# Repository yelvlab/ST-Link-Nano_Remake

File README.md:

# ST-Link-Nano_Remake
对稚晖君的ST-Link-Nano项目重新绘图和布局布线

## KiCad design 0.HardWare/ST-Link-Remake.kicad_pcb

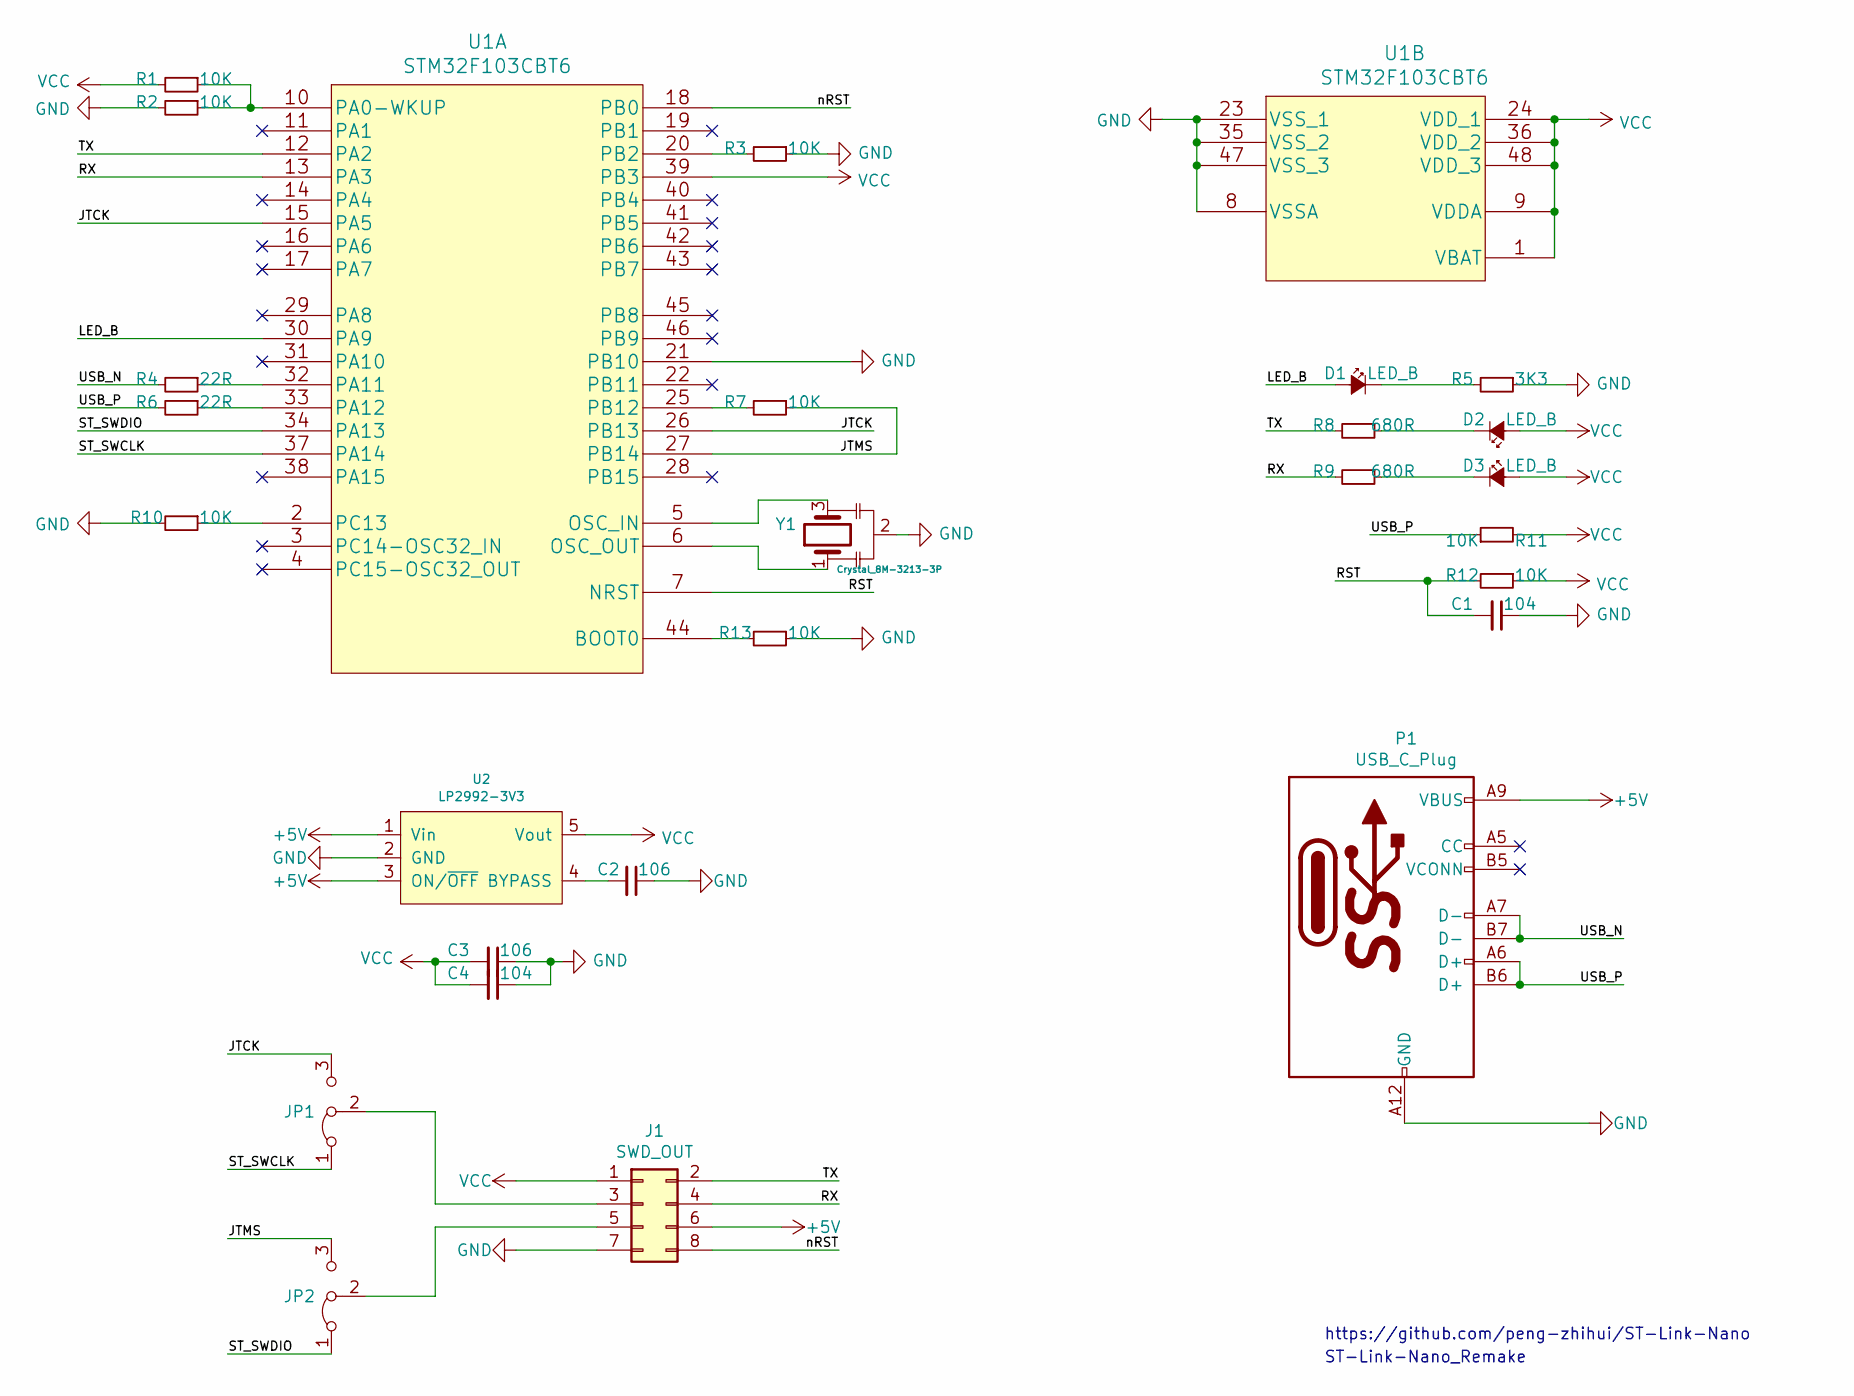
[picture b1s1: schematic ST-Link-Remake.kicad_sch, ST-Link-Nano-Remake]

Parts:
C1, C4: 104; C0402
C2, C3: 106; C0402
D1, D2, D3: LED_B; LED_0402_1005Metric
J1: SWD_OUT; PinSocket_2x04_P2.54mm_Vertical_SMD
JP1, JP2: Jumper_3_Bridged12; JUMPER_0402
P1: USB_C_Plug; USB_C_Receptacle_HRO_TYPE-C-31-M-12
R1, R2, R3, R7, R10, R11, R12, R13: 10K; R0402
R4, R6: 22R; R0402
R5: 3K3; R0402
R8, R9: 680R; R0402
U1: STM32F103CBT6; QFP-48_7x7_Pitch0.5mm
U2: LP2992-3V3; SOT-23-5
Y1: Crystal_8M-3213-3P; CSTCE16M

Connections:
+5V: J1.6, P1.A4 (VBUS), P1.A9 (VBUS), P1.B4 (VBUS), P1.B9 (VBUS), U2.1 (Vin), U2.3 (ON/~OFF)
/JTCK: JP1.3 (B), U1.15 (PA5), U1.26 (PB13)
/JTMS: JP2.3 (B), R7.1, U1.27 (PB14)
/LED_B: D1.2 (A), U1.30 (PA9)
/RST: C1.2, R12.2, U1.7 (NRST)
/RX: J1.4, R9.2, U1.13 (PA3)
/ST_SWCLK: JP1.1 (A), U1.37 (PA14)
/ST_SWDIO: JP2.1 (A), U1.34 (PA13)
/TX: J1.2, R8.2, U1.12 (PA2)
/USB_N: P1.A7 (D-), P1.B7 (D-), R4.2
/USB_P: P1.A6 (D+), P1.B6 (D+), R6.2, R11.1
/nRST: J1.8, U1.18 (PB0)
GND: C1.1, C2.1, C3.1, C4.1, J1.7, P1.A1 (GND), P1.A12 (GND), P1.B1 (GND), P1.B12 (GND), P1.S1 (GND), R2.2, R3.1, R5.1, R10.2, R13.1, U1.8 (VSSA), U1.21 (PB10), U1.23 (VSS_1), U1.35 (VSS_2), U1.47 (VSS_3), U2.2 (GND), Y1.2
unnamed: C2.2, U2.4 (BYPASS)
unnamed: D1.1 (K), R5.2
unnamed: D2.1 (K), R8.1
unnamed: D3.1 (K), R9.1
unnamed: J1.3, JP1.2 (C)
unnamed: J1.5, JP2.2 (C)
unnamed: R1.1, R2.1, U1.10 (PA0-WKUP)
unnamed: R3.2, U1.20 (PB2)
unnamed: R4.1, U1.32 (PA11)
unnamed: R6.1, U1.33 (PA12)
unnamed: R7.2, U1.25 (PB12)
unnamed: R10.1, U1.2 (PC13)
unnamed: R13.2, U1.44 (BOOT0)
unnamed: U1.5 (OSC_IN), Y1.3
unnamed: U1.6 (OSC_OUT), Y1.1
VCC: C3.2, C4.2, D2.2 (A), D3.2 (A), J1.1, R1.2, R11.2, R12.1, U1.1 (VBAT), U1.9 (VDDA), U1.24 (VDD_1), U1.36 (VDD_2), U1.39 (PB3), U1.48 (VDD_3), U2.5 (Vout)

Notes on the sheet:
https://github.com/peng-zhihui/ST-Link-Nano
ST-Link-Nano_Remake

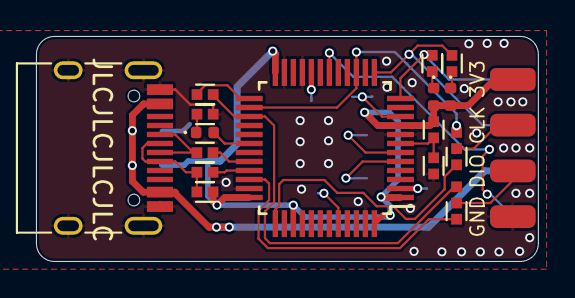
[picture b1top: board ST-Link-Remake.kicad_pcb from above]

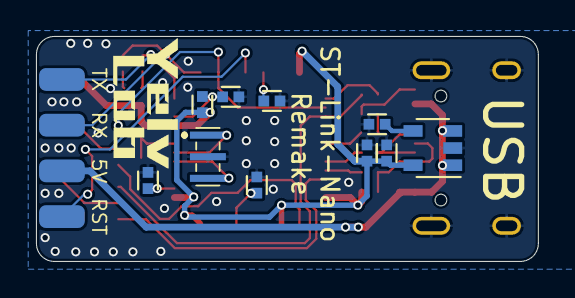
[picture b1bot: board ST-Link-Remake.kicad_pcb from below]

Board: 2 copper layers, 27.9 x 12.5 mm, 27 parts (10 on the bottom side), 29 nets.

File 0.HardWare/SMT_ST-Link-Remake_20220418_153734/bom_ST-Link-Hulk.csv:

Comment,Description,Designator,Footprint,LibRef,Pins,Quantity
"104","","C1,C4","C0402","","",2
"106","","C2,C3","C0402","","",2
"LED_B","LED SMD 0402 (1005 Metric), square (rectangular) end terminal, IPC_7351 nominal, (Body size source: http://www.tortai-tech.com/upload/download/20111020232333690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, generated with kicad-footprint-generator","D1,D2,D3","LED_0402_1005Metric","","",3
"SWD_OUT","surface-mounted straight socket strip, 2x04, 2.54mm pitch, double cols (from Kicad 4.0.7), script generated","J1","PinSocket_2x04_P2.54mm_Vertical_SMD","","",1
"Jumper_3_Bridged12","","JP1,JP2","JUMPER_0402","","",2
"USB_C_Plug","USB Type-C receptacle for USB 2.0 and PD, http://www.krhro.com/uploads/soft/180320/1-1P320120243.pdf","P1","USB_C_Receptacle_HRO_TYPE-C-31-M-12","","",1
"22R","","R4,R6","R0402","","",2
"3K3","","R5","R0402","","",1
"10K","","R7,R11,R12,R1,R2,R3,R10,R13","R0402","","",8
"680R","","R8,R9","R0402","","",2
"STM32F103CBT6","","U1","QFP-48_7x7_Pitch0.5mm","","",1
"LP2992-3V3","5-pin SOT23 package","U2","SOT-23-5","","",1
"Crystal_8M-3213-3P","CSTCE-V_C","Y1","CSTCE16M","","",1

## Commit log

2022-04-18 update hardware
